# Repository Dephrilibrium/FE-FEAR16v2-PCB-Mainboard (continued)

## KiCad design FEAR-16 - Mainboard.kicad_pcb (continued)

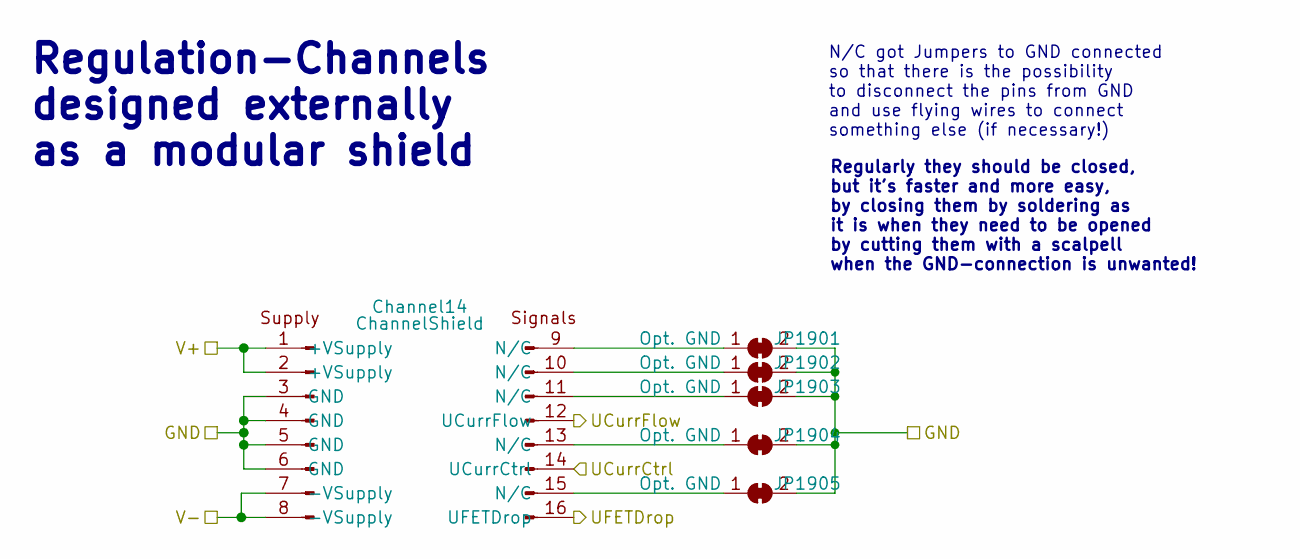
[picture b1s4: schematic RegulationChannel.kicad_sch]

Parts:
Channel14: ChannelShield
JP1901, JP1902, JP1903, JP1904, JP1905: Opt. GND; SolderJumper-2_P1.3mm_Open_RoundedPad1.0x1.5mm

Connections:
+15V: Channel14.1 (+VSupply), Channel14.2 (+VSupply); also elsewhere on the board
-15V: Channel14.7 (-VSupply), Channel14.8 (-VSupply); also elsewhere on the board
DAC14: Channel14.14 (UCurrCtrl); also elsewhere on the board
GNDPWR: Channel14.3 (GND), Channel14.4 (GND), Channel14.5 (GND), Channel14.6 (GND), JP1901.2 (B), JP1902.2 (B), JP1903.2 (B), JP1904.2 (B), JP1905.2 (B); also elsewhere on the board
unnamed: Channel14.9 (N/C), JP1901.1 (A)
unnamed: Channel14.10 (N/C), JP1902.1 (A)
unnamed: Channel14.11 (N/C), JP1903.1 (A)
unnamed: Channel14.13 (N/C), JP1904.1 (A)
unnamed: Channel14.15 (N/C), JP1905.1 (A)
VDrp14: Channel14.16 (UFETDrop); also elsewhere on the board
VShnt14: Channel14.12 (UCurrFlow); also elsewhere on the board

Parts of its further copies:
Channel0, Channel1, Channel2, Channel3, Channel4, Channel5, Channel6, Channel7, Channel8, Channel9, Channel10, Channel11, Channel12, Channel13, Channel15: ChannelShield
JP201, JP202, JP203, JP204, JP205, JP301, JP302, JP303, JP304, JP305, JP401, JP402, JP403, JP404, JP405, JP501, JP502, JP503, JP504, JP505, JP601, JP602, JP603, JP604, JP605, JP701, JP702, JP703, JP704, JP705, JP801, JP802, JP803, JP804, JP805, JP901, JP902, JP903, JP904, JP905, JP1001, JP1002, JP1003, JP1004, JP1005, JP1201, JP1202, JP1203, JP1204, JP1205, JP1501, JP1502, JP1503, JP1504, JP1505, JP1601, JP1602, JP1603, JP1604, JP1605, JP1701, JP1702, JP1703, JP1704, JP1705, JP1801, JP1802, JP1803, JP1804, JP1805, JP2001, JP2002, JP2003, JP2004, JP2005: Opt. GND; SolderJumper-2_P1.3mm_Open_RoundedPad1.0x1.5mm

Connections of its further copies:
+15V: Channel0.1 (+VSupply), Channel0.2 (+VSupply), Channel1.1 (+VSupply), Channel1.2 (+VSupply), Channel2.1 (+VSupply), Channel2.2 (+VSupply), Channel3.1 (+VSupply), Channel3.2 (+VSupply), Channel4.1 (+VSupply), Channel4.2 (+VSupply), Channel5.1 (+VSupply), Channel5.2 (+VSupply), Channel6.1 (+VSupply), Channel6.2 (+VSupply), Channel7.1 (+VSupply), Channel7.2 (+VSupply), Channel8.1 (+VSupply), Channel8.2 (+VSupply), Channel9.1 (+VSupply), Channel9.2 (+VSupply), Channel10.1 (+VSupply), Channel10.2 (+VSupply), Channel11.1 (+VSupply), Channel11.2 (+VSupply), Channel12.1 (+VSupply), Channel12.2 (+VSupply), Channel13.1 (+VSupply), Channel13.2 (+VSupply), Channel15.1 (+VSupply), Channel15.2 (+VSupply); also elsewhere on the board
-15V: Channel0.7 (-VSupply), Channel0.8 (-VSupply), Channel1.7 (-VSupply), Channel1.8 (-VSupply), Channel2.7 (-VSupply), Channel2.8 (-VSupply), Channel3.7 (-VSupply), Channel3.8 (-VSupply), Channel4.7 (-VSupply), Channel4.8 (-VSupply), Channel5.7 (-VSupply), Channel5.8 (-VSupply), Channel6.7 (-VSupply), Channel6.8 (-VSupply), Channel7.7 (-VSupply), Channel7.8 (-VSupply), Channel8.7 (-VSupply), Channel8.8 (-VSupply), Channel9.7 (-VSupply), Channel9.8 (-VSupply), Channel10.7 (-VSupply), Channel10.8 (-VSupply), Channel11.7 (-VSupply), Channel11.8 (-VSupply), Channel12.7 (-VSupply), Channel12.8 (-VSupply), Channel13.7 (-VSupply), Channel13.8 (-VSupply), Channel15.7 (-VSupply), Channel15.8 (-VSupply); also elsewhere on the board
DAC0: Channel0.14 (UCurrCtrl); also elsewhere on the board
DAC1: Channel1.14 (UCurrCtrl); also elsewhere on the board
DAC2: Channel2.14 (UCurrCtrl); also elsewhere on the board
DAC3: Channel3.14 (UCurrCtrl); also elsewhere on the board
DAC4: Channel4.14 (UCurrCtrl); also elsewhere on the board
DAC5: Channel5.14 (UCurrCtrl); also elsewhere on the board
DAC6: Channel6.14 (UCurrCtrl); also elsewhere on the board
DAC7: Channel7.14 (UCurrCtrl); also elsewhere on the board
DAC8: Channel8.14 (UCurrCtrl); also elsewhere on the board
DAC9: Channel9.14 (UCurrCtrl); also elsewhere on the board
DAC10: Channel10.14 (UCurrCtrl); also elsewhere on the board
DAC11: Channel11.14 (UCurrCtrl); also elsewhere on the board
DAC12: Channel12.14 (UCurrCtrl); also elsewhere on the board
DAC13: Channel13.14 (UCurrCtrl); also elsewhere on the board
DAC15: Channel15.14 (UCurrCtrl); also elsewhere on the board
GNDPWR: Channel0.3 (GND), Channel0.4 (GND), Channel0.5 (GND), Channel0.6 (GND), Channel1.3 (GND), Channel1.4 (GND), Channel1.5 (GND), Channel1.6 (GND), Channel2.3 (GND), Channel2.4 (GND), Channel2.5 (GND), Channel2.6 (GND), Channel3.3 (GND), Channel3.4 (GND), Channel3.5 (GND), Channel3.6 (GND), Channel4.3 (GND), Channel4.4 (GND), Channel4.5 (GND), Channel4.6 (GND), Channel5.3 (GND), Channel5.4 (GND), Channel5.5 (GND), Channel5.6 (GND), Channel6.3 (GND), Channel6.4 (GND), Channel6.5 (GND), Channel6.6 (GND), Channel7.3 (GND), Channel7.4 (GND), Channel7.5 (GND), Channel7.6 (GND), Channel8.3 (GND), Channel8.4 (GND), Channel8.5 (GND), Channel8.6 (GND), Channel9.3 (GND), Channel9.4 (GND), Channel9.5 (GND), Channel9.6 (GND), Channel10.3 (GND), Channel10.4 (GND), Channel10.5 (GND), Channel10.6 (GND), Channel11.3 (GND), Channel11.4 (GND), Channel11.5 (GND), Channel11.6 (GND), Channel12.3 (GND), Channel12.4 (GND), Channel12.5 (GND), Channel12.6 (GND), Channel13.3 (GND), Channel13.4 (GND), Channel13.5 (GND), Channel13.6 (GND), Channel15.3 (GND), Channel15.4 (GND), Channel15.5 (GND), Channel15.6 (GND), JP201.2 (B), JP202.2 (B), JP203.2 (B), JP204.2 (B), JP205.2 (B), JP301.2 (B), JP302.2 (B), JP303.2 (B), JP304.2 (B), JP305.2 (B), JP401.2 (B), JP402.2 (B), JP403.2 (B), JP404.2 (B), JP405.2 (B), JP501.2 (B), JP502.2 (B), JP503.2 (B), JP504.2 (B), JP505.2 (B), JP601.2 (B), JP602.2 (B), JP603.2 (B), JP604.2 (B), JP605.2 (B), JP701.2 (B), JP702.2 (B), JP703.2 (B), JP704.2 (B), JP705.2 (B), JP801.2 (B), JP802.2 (B), JP803.2 (B), JP804.2 (B), JP805.2 (B), JP901.2 (B), JP902.2 (B), JP903.2 (B), JP904.2 (B), JP905.2 (B), JP1001.2 (B), JP1002.2 (B), JP1003.2 (B), JP1004.2 (B), JP1005.2 (B), JP1201.2 (B), JP1202.2 (B), JP1203.2 (B), JP1204.2 (B), JP1205.2 (B), JP1501.2 (B), JP1502.2 (B), JP1503.2 (B), JP1504.2 (B), JP1505.2 (B), JP1601.2 (B), JP1602.2 (B), JP1603.2 (B), JP1604.2 (B), JP1605.2 (B), JP1701.2 (B), JP1702.2 (B), JP1703.2 (B), JP1704.2 (B), JP1705.2 (B), JP1801.2 (B), JP1802.2 (B), JP1803.2 (B), JP1804.2 (B), JP1805.2 (B), JP2001.2 (B), JP2002.2 (B), JP2003.2 (B), JP2004.2 (B), JP2005.2 (B); also elsewhere on the board
unnamed: Channel1.9 (N/C), JP201.1 (A)
unnamed: Channel1.10 (N/C), JP202.1 (A)
unnamed: Channel1.11 (N/C), JP203.1 (A)
unnamed: Channel1.13 (N/C), JP204.1 (A)
unnamed: Channel1.15 (N/C), JP205.1 (A)
unnamed: Channel2.9 (N/C), JP301.1 (A)
unnamed: Channel2.10 (N/C), JP302.1 (A)
unnamed: Channel2.11 (N/C), JP303.1 (A)
unnamed: Channel2.13 (N/C), JP304.1 (A)
unnamed: Channel2.15 (N/C), JP305.1 (A)
unnamed: Channel3.9 (N/C), JP401.1 (A)
unnamed: Channel3.10 (N/C), JP402.1 (A)
unnamed: Channel3.11 (N/C), JP403.1 (A)
unnamed: Channel3.13 (N/C), JP404.1 (A)
unnamed: Channel3.15 (N/C), JP405.1 (A)
unnamed: Channel4.9 (N/C), JP501.1 (A)
unnamed: Channel4.10 (N/C), JP502.1 (A)
unnamed: Channel4.11 (N/C), JP503.1 (A)
unnamed: Channel4.13 (N/C), JP504.1 (A)
unnamed: Channel4.15 (N/C), JP505.1 (A)
unnamed: Channel5.9 (N/C), JP601.1 (A)
unnamed: Channel5.10 (N/C), JP602.1 (A)
unnamed: Channel5.11 (N/C), JP603.1 (A)
unnamed: Channel5.13 (N/C), JP604.1 (A)
unnamed: Channel5.15 (N/C), JP605.1 (A)
unnamed: Channel6.9 (N/C), JP701.1 (A)
unnamed: Channel6.10 (N/C), JP702.1 (A)
unnamed: Channel6.11 (N/C), JP703.1 (A)
unnamed: Channel6.13 (N/C), JP704.1 (A)
unnamed: Channel6.15 (N/C), JP705.1 (A)
unnamed: Channel7.9 (N/C), JP801.1 (A)
unnamed: Channel7.10 (N/C), JP802.1 (A)
unnamed: Channel7.11 (N/C), JP803.1 (A)
unnamed: Channel7.13 (N/C), JP804.1 (A)
unnamed: Channel7.15 (N/C), JP805.1 (A)
unnamed: Channel8.9 (N/C), JP901.1 (A)
unnamed: Channel8.10 (N/C), JP902.1 (A)
unnamed: Channel8.11 (N/C), JP903.1 (A)
unnamed: Channel8.13 (N/C), JP904.1 (A)
unnamed: Channel8.15 (N/C), JP905.1 (A)
unnamed: Channel9.9 (N/C), JP1001.1 (A)
unnamed: Channel9.10 (N/C), JP1002.1 (A)
unnamed: Channel9.11 (N/C), JP1003.1 (A)
unnamed: Channel9.13 (N/C), JP1004.1 (A)
unnamed: Channel9.15 (N/C), JP1005.1 (A)
unnamed: Channel10.9 (N/C), JP1201.1 (A)
unnamed: Channel10.10 (N/C), JP1202.1 (A)
unnamed: Channel10.11 (N/C), JP1203.1 (A)
unnamed: Channel10.13 (N/C), JP1204.1 (A)
unnamed: Channel10.15 (N/C), JP1205.1 (A)
unnamed: Channel11.9 (N/C), JP1501.1 (A)
unnamed: Channel11.10 (N/C), JP1502.1 (A)
unnamed: Channel11.11 (N/C), JP1503.1 (A)
unnamed: Channel11.13 (N/C), JP1504.1 (A)
unnamed: Channel11.15 (N/C), JP1505.1 (A)
unnamed: Channel12.9 (N/C), JP1601.1 (A)
unnamed: Channel12.10 (N/C), JP1602.1 (A)
unnamed: Channel12.11 (N/C), JP1603.1 (A)
unnamed: Channel12.13 (N/C), JP1604.1 (A)
unnamed: Channel12.15 (N/C), JP1605.1 (A)
unnamed: Channel13.9 (N/C), JP1701.1 (A)
unnamed: Channel13.10 (N/C), JP1702.1 (A)
unnamed: Channel13.11 (N/C), JP1703.1 (A)
unnamed: Channel13.13 (N/C), JP1704.1 (A)
unnamed: Channel13.15 (N/C), JP1705.1 (A)
unnamed: Channel0.9 (N/C), JP1801.1 (A)
unnamed: Channel0.10 (N/C), JP1802.1 (A)
unnamed: Channel0.11 (N/C), JP1803.1 (A)
unnamed: Channel0.13 (N/C), JP1804.1 (A)
unnamed: Channel0.15 (N/C), JP1805.1 (A)
unnamed: Channel15.9 (N/C), JP2001.1 (A)
unnamed: Channel15.10 (N/C), JP2002.1 (A)
unnamed: Channel15.11 (N/C), JP2003.1 (A)
unnamed: Channel15.13 (N/C), JP2004.1 (A)
unnamed: Channel15.15 (N/C), JP2005.1 (A)
VDrp0: Channel0.16 (UFETDrop); also elsewhere on the board
VDrp1: Channel1.16 (UFETDrop); also elsewhere on the board
VDrp2: Channel2.16 (UFETDrop); also elsewhere on the board
VDrp3: Channel3.16 (UFETDrop); also elsewhere on the board
VDrp4: Channel4.16 (UFETDrop); also elsewhere on the board
VDrp5: Channel5.16 (UFETDrop); also elsewhere on the board
VDrp6: Channel6.16 (UFETDrop); also elsewhere on the board
VDrp7: Channel7.16 (UFETDrop); also elsewhere on the board
VDrp8: Channel8.16 (UFETDrop); also elsewhere on the board
VDrp9: Channel9.16 (UFETDrop); also elsewhere on the board
VDrp10: Channel10.16 (UFETDrop); also elsewhere on the board
VDrp11: Channel11.16 (UFETDrop); also elsewhere on the board
VDrp12: Channel12.16 (UFETDrop); also elsewhere on the board
VDrp13: Channel13.16 (UFETDrop); also elsewhere on the board
VDrp15: Channel15.16 (UFETDrop); also elsewhere on the board
VShnt0: Channel0.12 (UCurrFlow); also elsewhere on the board
VShnt1: Channel1.12 (UCurrFlow); also elsewhere on the board
VShnt2: Channel2.12 (UCurrFlow); also elsewhere on the board
VShnt3: Channel3.12 (UCurrFlow); also elsewhere on the board
VShnt4: Channel4.12 (UCurrFlow); also elsewhere on the board
VShnt5: Channel5.12 (UCurrFlow); also elsewhere on the board
VShnt6: Channel6.12 (UCurrFlow); also elsewhere on the board
VShnt7: Channel7.12 (UCurrFlow); also elsewhere on the board
VShnt8: Channel8.12 (UCurrFlow); also elsewhere on the board
VShnt9: Channel9.12 (UCurrFlow); also elsewhere on the board
VShnt10: Channel10.12 (UCurrFlow); also elsewhere on the board
VShnt11: Channel11.12 (UCurrFlow); also elsewhere on the board
VShnt12: Channel12.12 (UCurrFlow); also elsewhere on the board
VShnt13: Channel13.12 (UCurrFlow); also elsewhere on the board
VShnt15: Channel15.12 (UCurrFlow); also elsewhere on the board

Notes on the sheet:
Regulation-Channels designed externally as a modular shield
N/C got Jumpers to GND connected so that there is the possibility to disconnect the pins from GND and use flying wires to connect something else (if necessary!)
Regularly they should be closed, but it's faster and more easy, by closing them by soldering as it is when they need to be opened by cutting them with a scalpell when the GND-connection is unwanted!

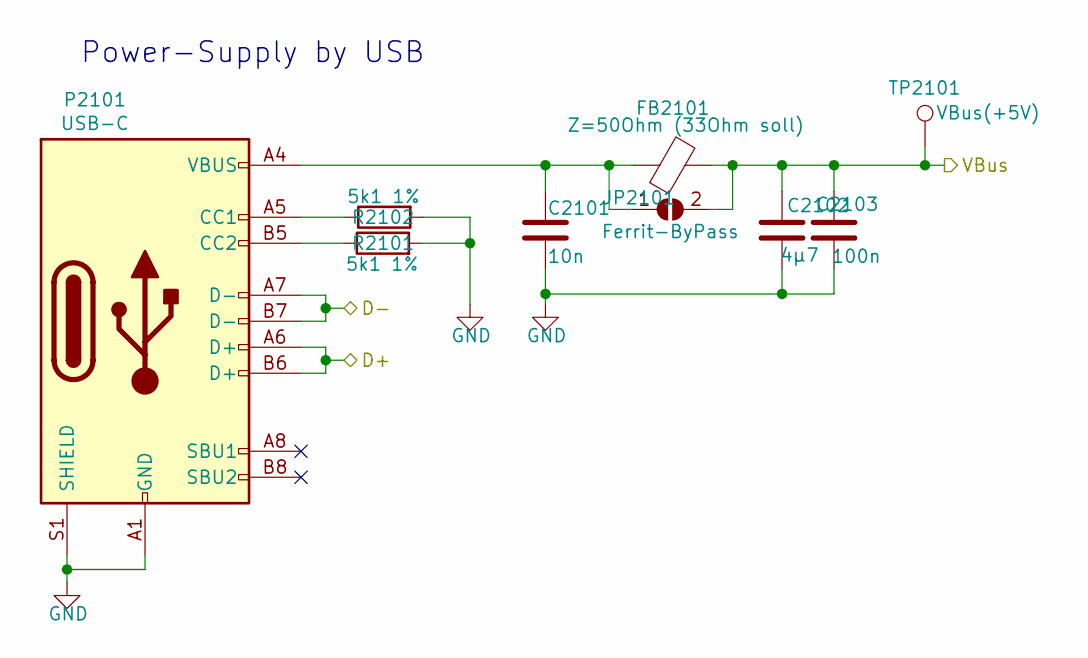
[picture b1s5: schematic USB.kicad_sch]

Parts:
C2101: 10n; C_0603_1608Metric
C2102: 4µ7; CP_EIA-3528-21_Kemet-B
C2103: 100n; C_0603_1608Metric
FB2101: Z=50Ohm (33Ohm soll); L_1206_3216Metric
JP2101: Ferrit-ByPass; SolderJumper-2_P1.3mm_Open_RoundedPad1.0x1.5mm
P2101: USB-C; USB_C_Receptacle_HRO_TYPE-C-31-M-12
R2101, R2102: 5k1 1%; R_0603_1608Metric
TP2101: VBus(+5V); TestPoint_Pad_D1.5mm

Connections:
D+: P2101.A6 (D+), P2101.B6 (D+); also elsewhere on the board
D-: P2101.A7 (D-), P2101.B7 (D-); also elsewhere on the board
GND: C2101.2, C2102.2, C2103.2, P2101.A1 (GND), P2101.A12 (GND), P2101.B1 (GND), P2101.B12 (GND), P2101.S1 (SHIELD), R2101.2, R2102.2; also elsewhere on the board
unnamed: C2101.1, FB2101.1, JP2101.1 (A), P2101.A4 (VBUS), P2101.A9 (VBUS), P2101.B4 (VBUS), P2101.B9 (VBUS)
unnamed: P2101.A5 (CC1), R2102.1
unnamed: P2101.B5 (CC2), R2101.1
VBUS (5V): C2102.1, C2103.1, FB2101.2, JP2101.2 (B), TP2101.1; also elsewhere on the board

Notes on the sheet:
Power-Supply by USB

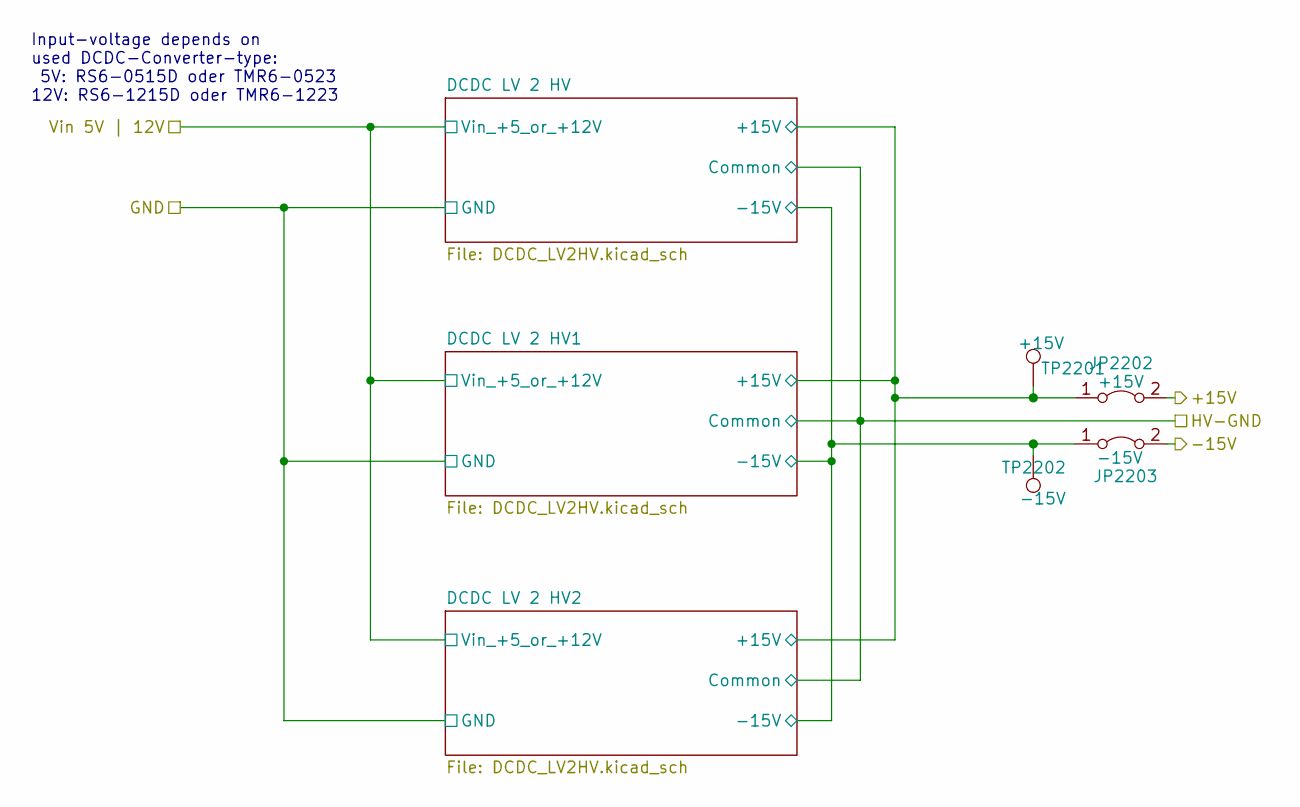
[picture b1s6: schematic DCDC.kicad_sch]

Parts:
JP2202: +15V; PinHeader_1x02_P2.54mm_Vertical
JP2203: -15V; PinHeader_1x02_P2.54mm_Vertical
TP2201: +15V; TestPoint_Pad_D1.5mm
TP2202: -15V; TestPoint_Pad_D1.5mm

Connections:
+15V: JP2202.2 (B); also elsewhere on the board
-15V: JP2203.2 (B); also elsewhere on the board
/DCDC PC -> HV-Reg/DCDC LV 2 HV/+15V: JP2202.1 (A), TP2201.1; also elsewhere on the board
/DCDC PC -> HV-Reg/DCDC LV 2 HV/-15V: JP2203.1 (A), TP2202.1; also elsewhere on the board

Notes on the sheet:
Input-voltage depends on used DCDC-Converter-type: 5V: RS6-0515D oder TMR6-0523 12V: RS6-1215D oder TMR6-1223

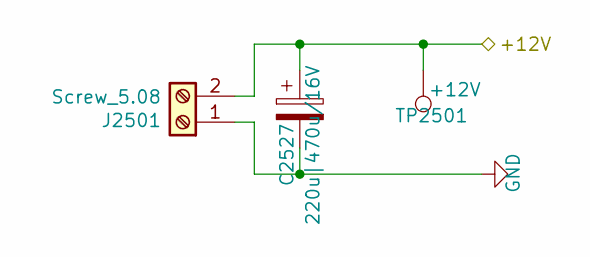
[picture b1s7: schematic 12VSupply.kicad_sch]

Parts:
C2527: 220u|470u/16V; CP_Elec_10x10.5
J2501: Screw_5.08; TerminalBlock_RND_205-00232_1x02_P5.08mm_Horizontal
TP2501: +12V; TestPoint_Pad_D1.5mm

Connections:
GND: C2527.2, J2501.1; also elsewhere on the board
Vin_12V: C2527.1, J2501.2, TP2501.1; also elsewhere on the board

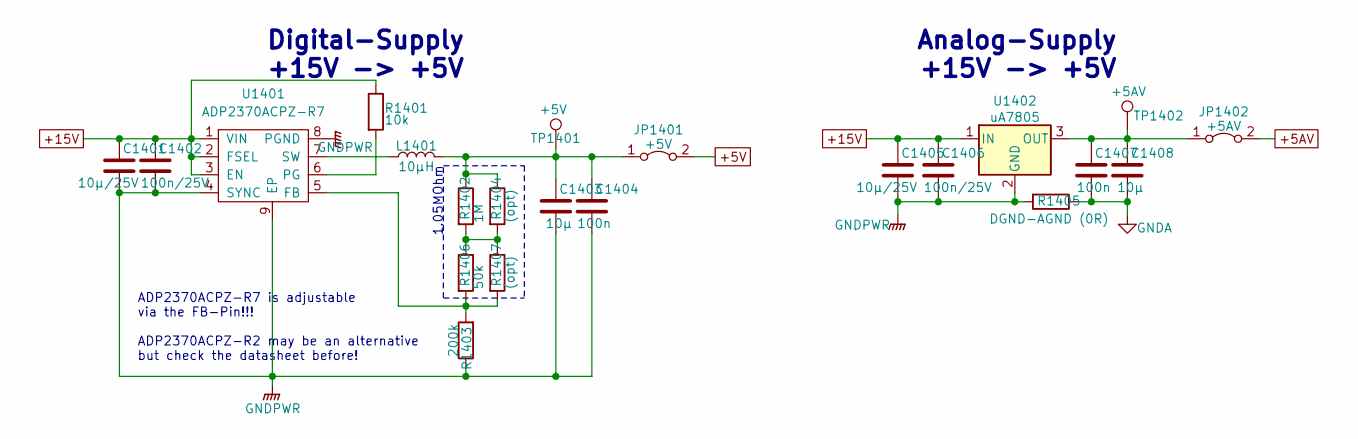
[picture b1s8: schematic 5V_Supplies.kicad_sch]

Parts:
C1401, C1405: 10µ/25V; C_0805_2012Metric
C1402, C1406: 100n/25V; C_0603_1608Metric
C1403, C1408: 10µ; C_0805_2012Metric
C1404, C1407: 100n; C_0603_1608Metric
JP1401: +5V; PinHeader_1x02_P2.54mm_Vertical
JP1402: +5AV; PinHeader_1x02_P2.54mm_Vertical
L1401: 10µH; L_Coilcraft_XxL4040
R1401: 10k; R_0603_1608Metric
R1402: 1M; R_0603_1608Metric
R1403: 200k; R_0603_1608Metric
R1404, R1407: (opt); R_0603_1608Metric
R1405: DGND-AGND (0R); R_0603_1608Metric
R1406: 50k; R_0603_1608Metric
TP1401: +5V; TestPoint_Pad_D1.5mm
TP1402: +5AV; TestPoint_Pad_D1.5mm
U1401: ADP2370ACPZ-R7; LFCSP-8-1EP_3x3mm_P0.5mm_EP1.6x2.34mm_ThermalVias
U1402: uA7805; SOT-223-3_TabPin2

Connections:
+5AV: JP1402.2 (B); also elsewhere on the board
+5V: JP1401.2 (B); also elsewhere on the board
+15V: C1401.1, C1402.1, C1405.1, C1406.1, R1401.1, U1401.1 (VIN), U1401.2 (FSEL), U1401.3 (EN), U1402.1 (IN); also elsewhere on the board
GNDA: C1407.2, C1408.2, R1405.1; also elsewhere on the board
GNDPWR: C1401.2, C1402.2, C1403.2, C1404.2, C1405.2, C1406.2, R1403.1, R1405.2, U1401.4 (SYNC), U1401.8 (PGND), U1401.9 (EP), U1402.2 (GND); also elsewhere on the board
unnamed: C1403.1, C1404.1, JP1401.1 (A), L1401.2, R1402.1, R1404.1, TP1401.1
unnamed: C1407.1, C1408.1, JP1402.1 (A), TP1402.1, U1402.3 (OUT)
unnamed: R1402.2, R1404.2, R1406.1, R1407.1
unnamed: R1403.2, R1406.2, R1407.2, U1401.5 (FB)
unnamed: R1401.2, U1401.6 (PG)
unnamed: L1401.1, U1401.7 (SW)

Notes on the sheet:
1.05MOhm
Digital-Supply +15V -> +5V
ADP2370ACPZ-R7 is adjustable via the FB-Pin!!! ADP2370ACPZ-R2 may be an alternative but check the datasheet before!
Analog-Supply +15V -> +5V

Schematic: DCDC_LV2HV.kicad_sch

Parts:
C2104: 10µ/16V; C_0805_2012Metric
C2105: 100n/16V; C_0603_1608Metric
C2106: 10µ/25V; C_0805_2012Metric
C2107: 10µF/25V; C_0805_2012Metric
C2108, C2109: 100n/25V; C_0603_1608Metric
D2101, D2102: BAT54(W); SOT-323_SC-70
PS2101: 5V/12V -> +-15V DCDC; TMR_6-0523

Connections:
/DCDC PC -> HV-Reg/DCDC LV 2 HV/+15V: D2101.3 (K); also elsewhere on the board
/DCDC PC -> HV-Reg/DCDC LV 2 HV/-15V: D2102.1 (A); also elsewhere on the board
/DCDC PC -> HV-Reg/Vin 5V | 12V: C2104.2, C2105.1, PS2101.2 (+VIN); also elsewhere on the board
GND: C2104.1, C2105.2, PS2101.1 (-VIN); also elsewhere on the board
GNDPWR: C2106.1, C2107.2, C2108.2, C2109.1, PS2101.7 (Common); also elsewhere on the board
unnamed: C2106.2, C2108.1, D2101.1 (A), PS2101.6 (+VOUT)
unnamed: C2107.1, C2109.2, D2102.3 (K), PS2101.8 (-VOUT)

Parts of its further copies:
C2227, C2601: 10µ/16V; C_0805_2012Metric
C2228, C2602: 100n/16V; C_0603_1608Metric
C2229, C2603: 10µ/25V; C_0805_2012Metric
C2230, C2604: 10µF/25V; C_0805_2012Metric
C2231, C2232, C2605, C2606: 100n/25V; C_0603_1608Metric
D2201, D2202, D2601, D2602: BAT54(W); SOT-323_SC-70
PS2201, PS2601: 5V/12V -> +-15V DCDC; TMR_6-0523

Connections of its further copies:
/DCDC PC -> HV-Reg/DCDC LV 2 HV/+15V: D2201.3 (K), D2601.3 (K); also elsewhere on the board
/DCDC PC -> HV-Reg/DCDC LV 2 HV/-15V: D2202.1 (A), D2602.1 (A); also elsewhere on the board
/DCDC PC -> HV-Reg/Vin 5V | 12V: C2227.2, C2228.1, C2601.2, C2602.1, PS2201.2 (+VIN), PS2601.2 (+VIN); also elsewhere on the board
GND: C2227.1, C2228.2, C2601.1, C2602.2, PS2201.1 (-VIN), PS2601.1 (-VIN); also elsewhere on the board
GNDPWR: C2229.1, C2230.2, C2231.2, C2232.1, C2603.1, C2604.2, C2605.2, C2606.1, PS2201.7 (Common), PS2601.7 (Common); also elsewhere on the board
unnamed: C2229.2, C2231.1, D2201.1 (A), PS2201.6 (+VOUT)
unnamed: C2230.1, C2232.2, D2202.3 (K), PS2201.8 (-VOUT)
unnamed: C2603.2, C2605.1, D2601.1 (A), PS2601.6 (+VOUT)
unnamed: C2604.1, C2606.2, D2602.3 (K), PS2601.8 (-VOUT)

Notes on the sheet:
Input-voltage depends on used DCDC-Converter-type: 5V: RS6-0515D oder TMR6-0523 12V: RS6-1215D oder TMR6-1223

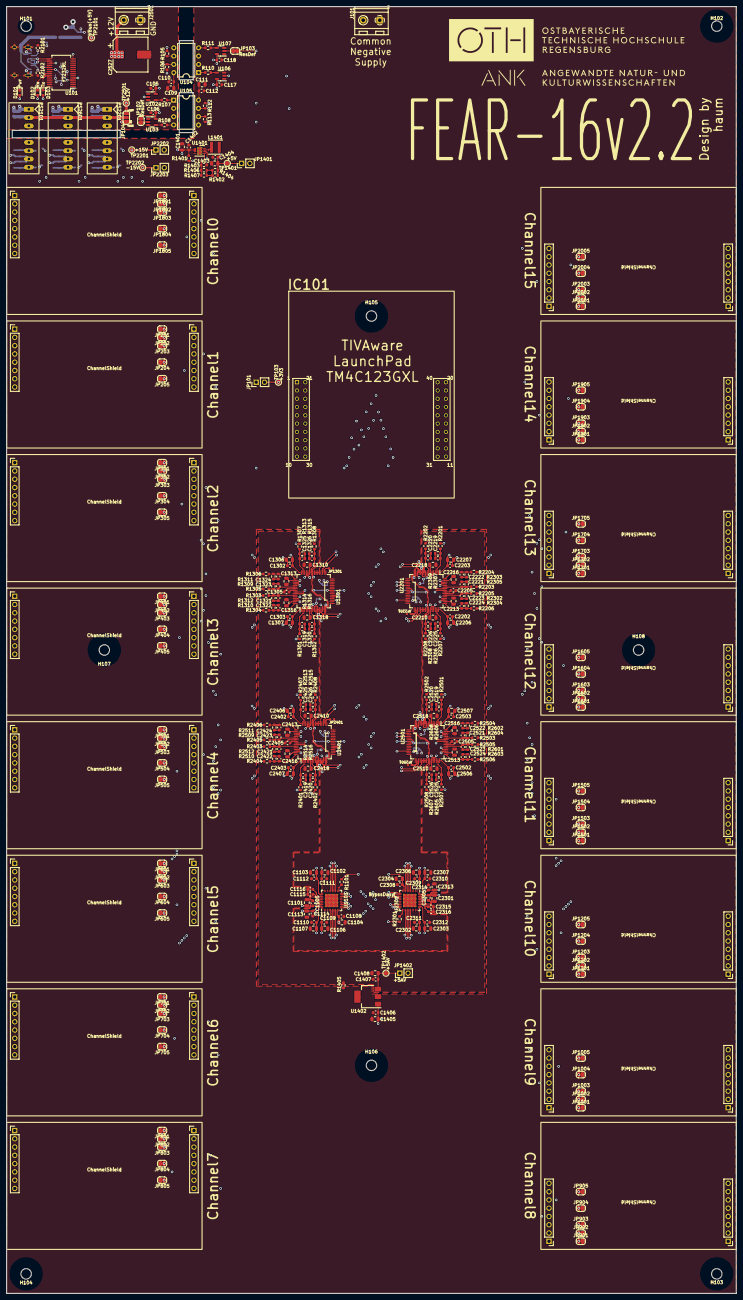
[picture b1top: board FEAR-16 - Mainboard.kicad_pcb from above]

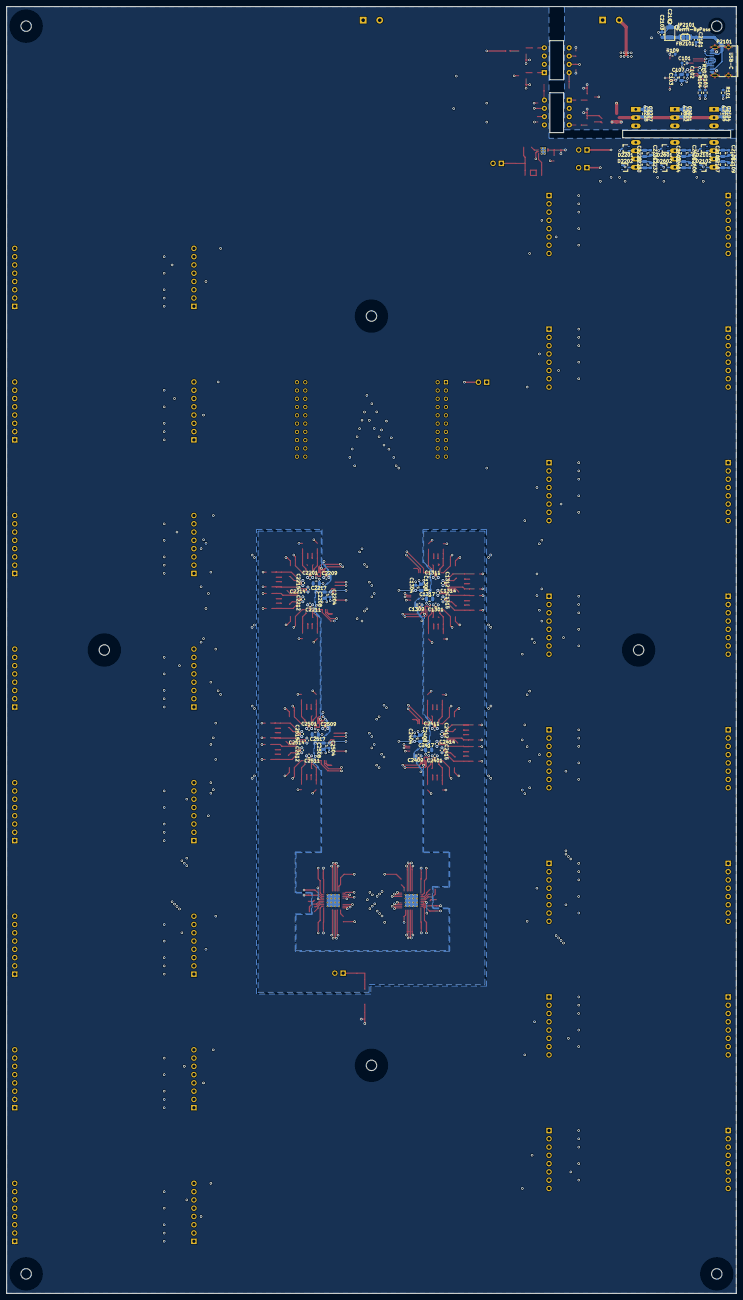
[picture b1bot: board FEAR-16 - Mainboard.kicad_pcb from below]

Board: 4 copper layers, 224.0 x 395.0 mm, 423 parts (75 on the bottom side), 266 nets.

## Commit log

2023-07-03 Added LICENSE.md
2023-07-20 FEAR-16 V2.2
    PCB-Changes:
    - Added rudimentary "load-balancer" (not really a balancer, but should avoid the DC/DC from regulating against each other!)
    - Added optional GND-jumpers to the N/C pins of the shields
    - Modified amplification adjustment:
    -> Added a offset resistor in row to the trim-poti for amplification for finer amp-tuning
    -> Reduced trim-poti-value from 1Meg -> 50k (20x finer adjustment-range)
2024-08-07 Fixed ADP2370 designator
    ADP2370 has a bunch of fixed output voltages and an adjustable model.
    We use the adjustable model, so we fixed the name matching with the correct model-name.
2024-09-13 Finished README.md
    - Adjustment in .gitignore
    - Finished first README.md attempt
    - Added extra comments to "5V_Supplies"
